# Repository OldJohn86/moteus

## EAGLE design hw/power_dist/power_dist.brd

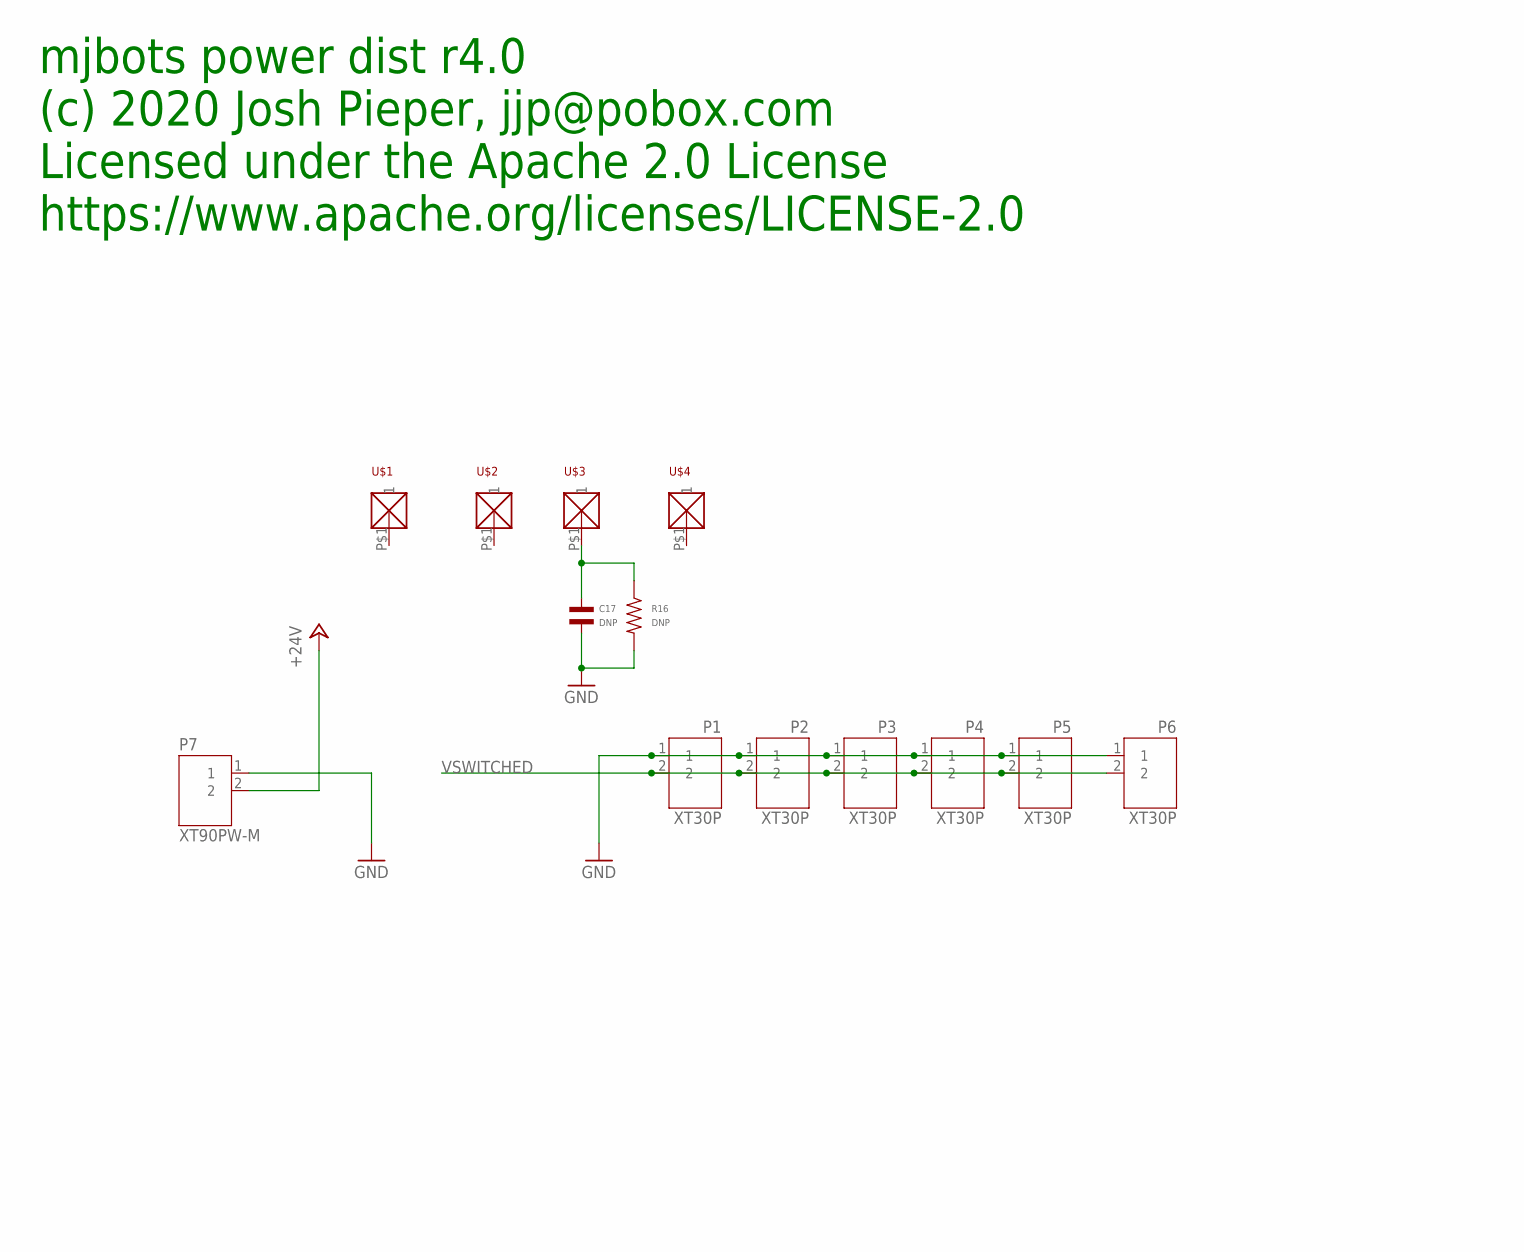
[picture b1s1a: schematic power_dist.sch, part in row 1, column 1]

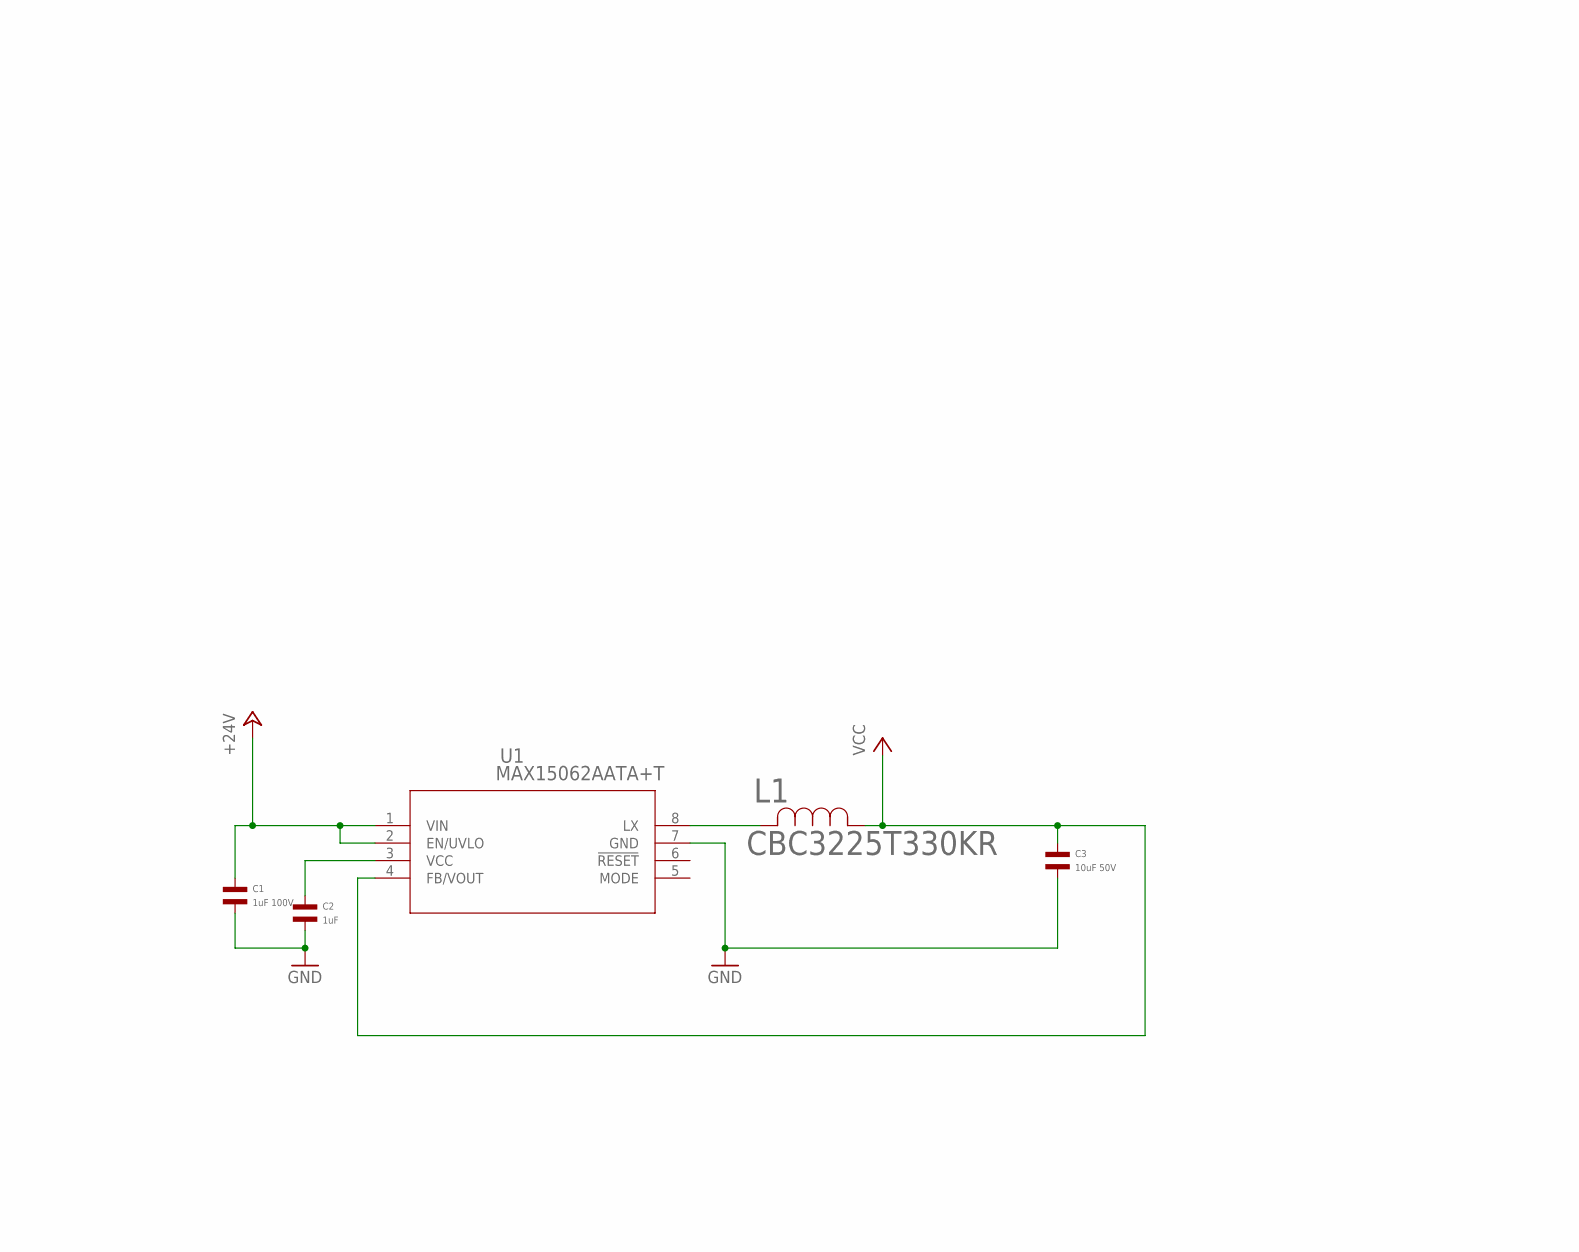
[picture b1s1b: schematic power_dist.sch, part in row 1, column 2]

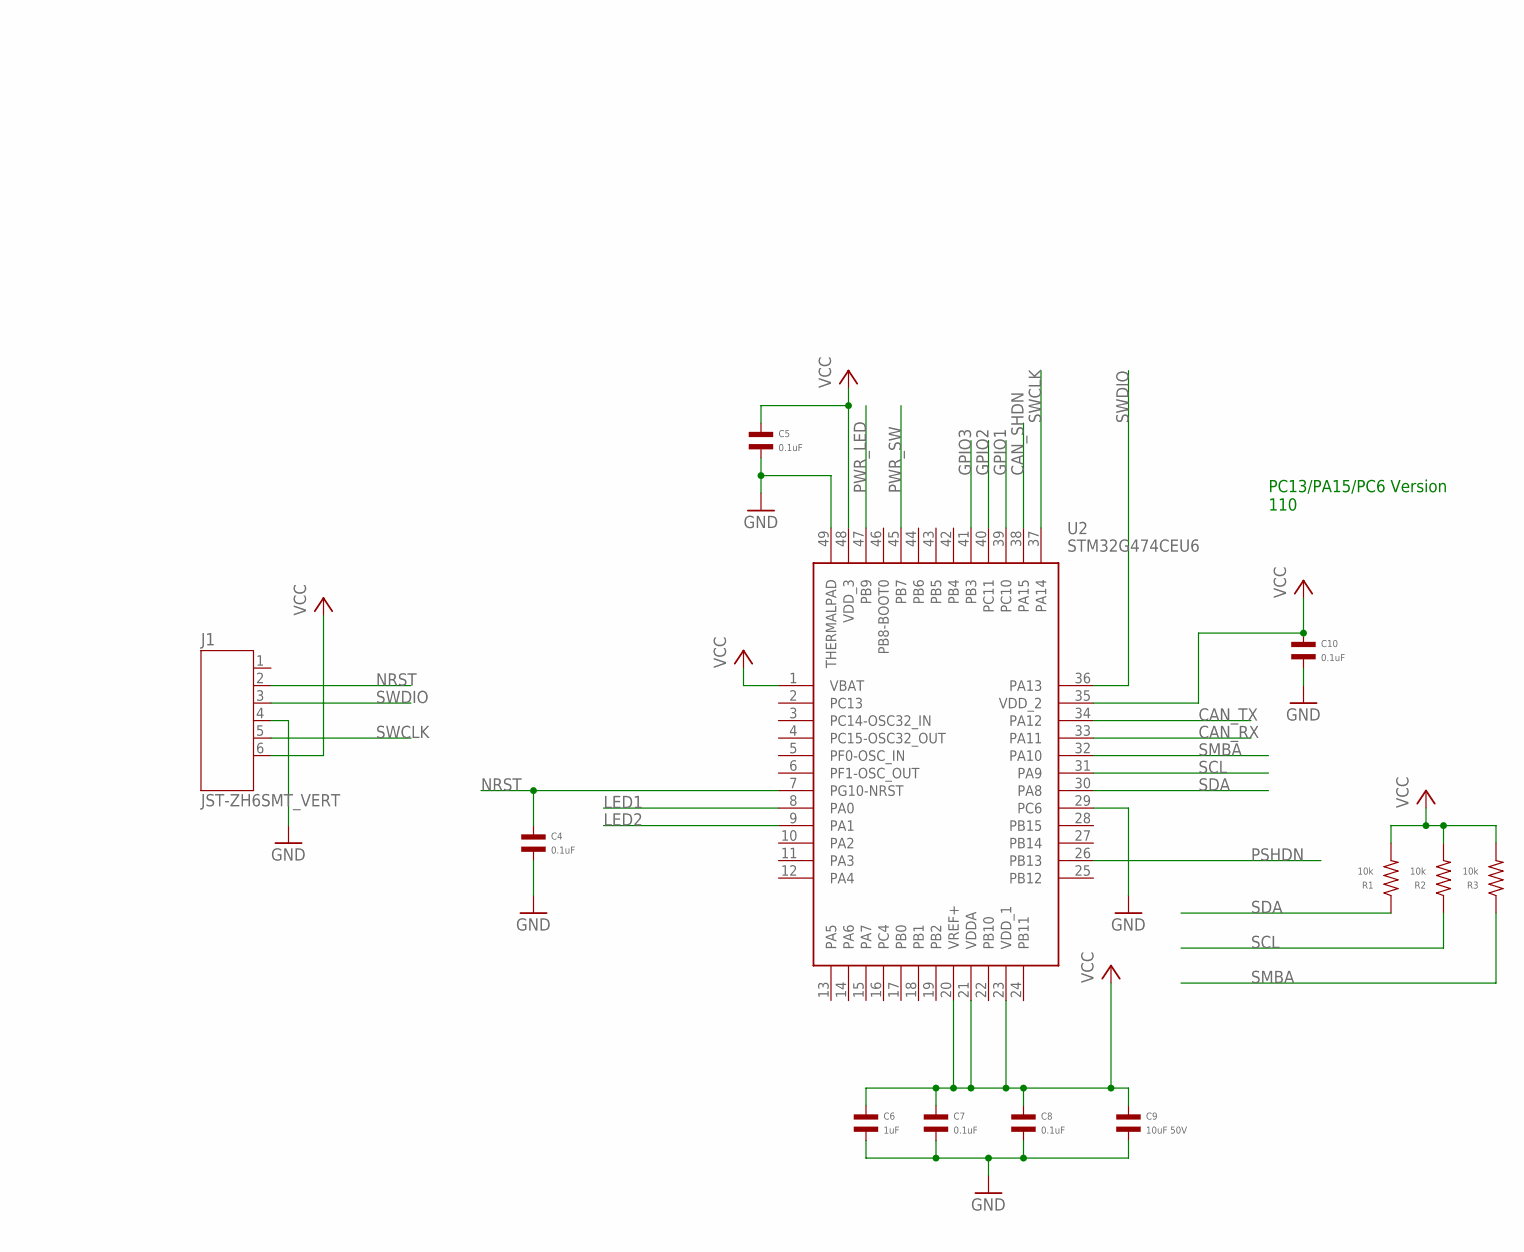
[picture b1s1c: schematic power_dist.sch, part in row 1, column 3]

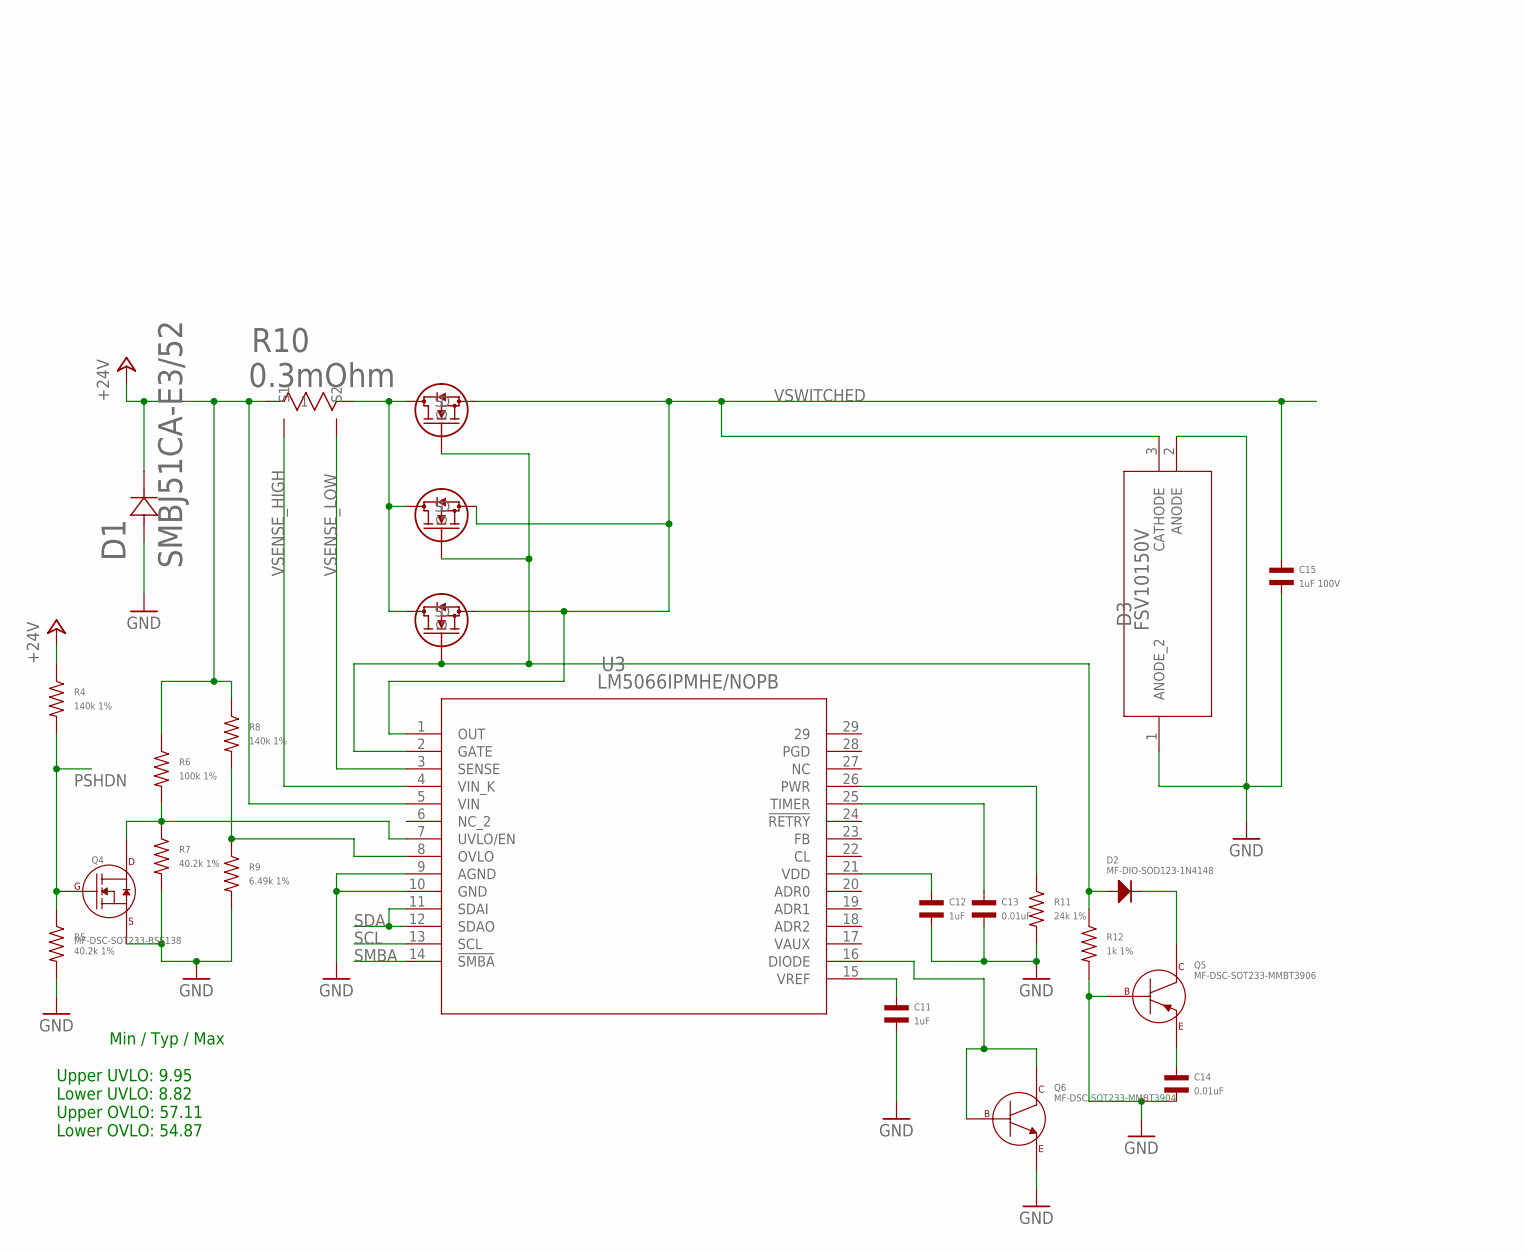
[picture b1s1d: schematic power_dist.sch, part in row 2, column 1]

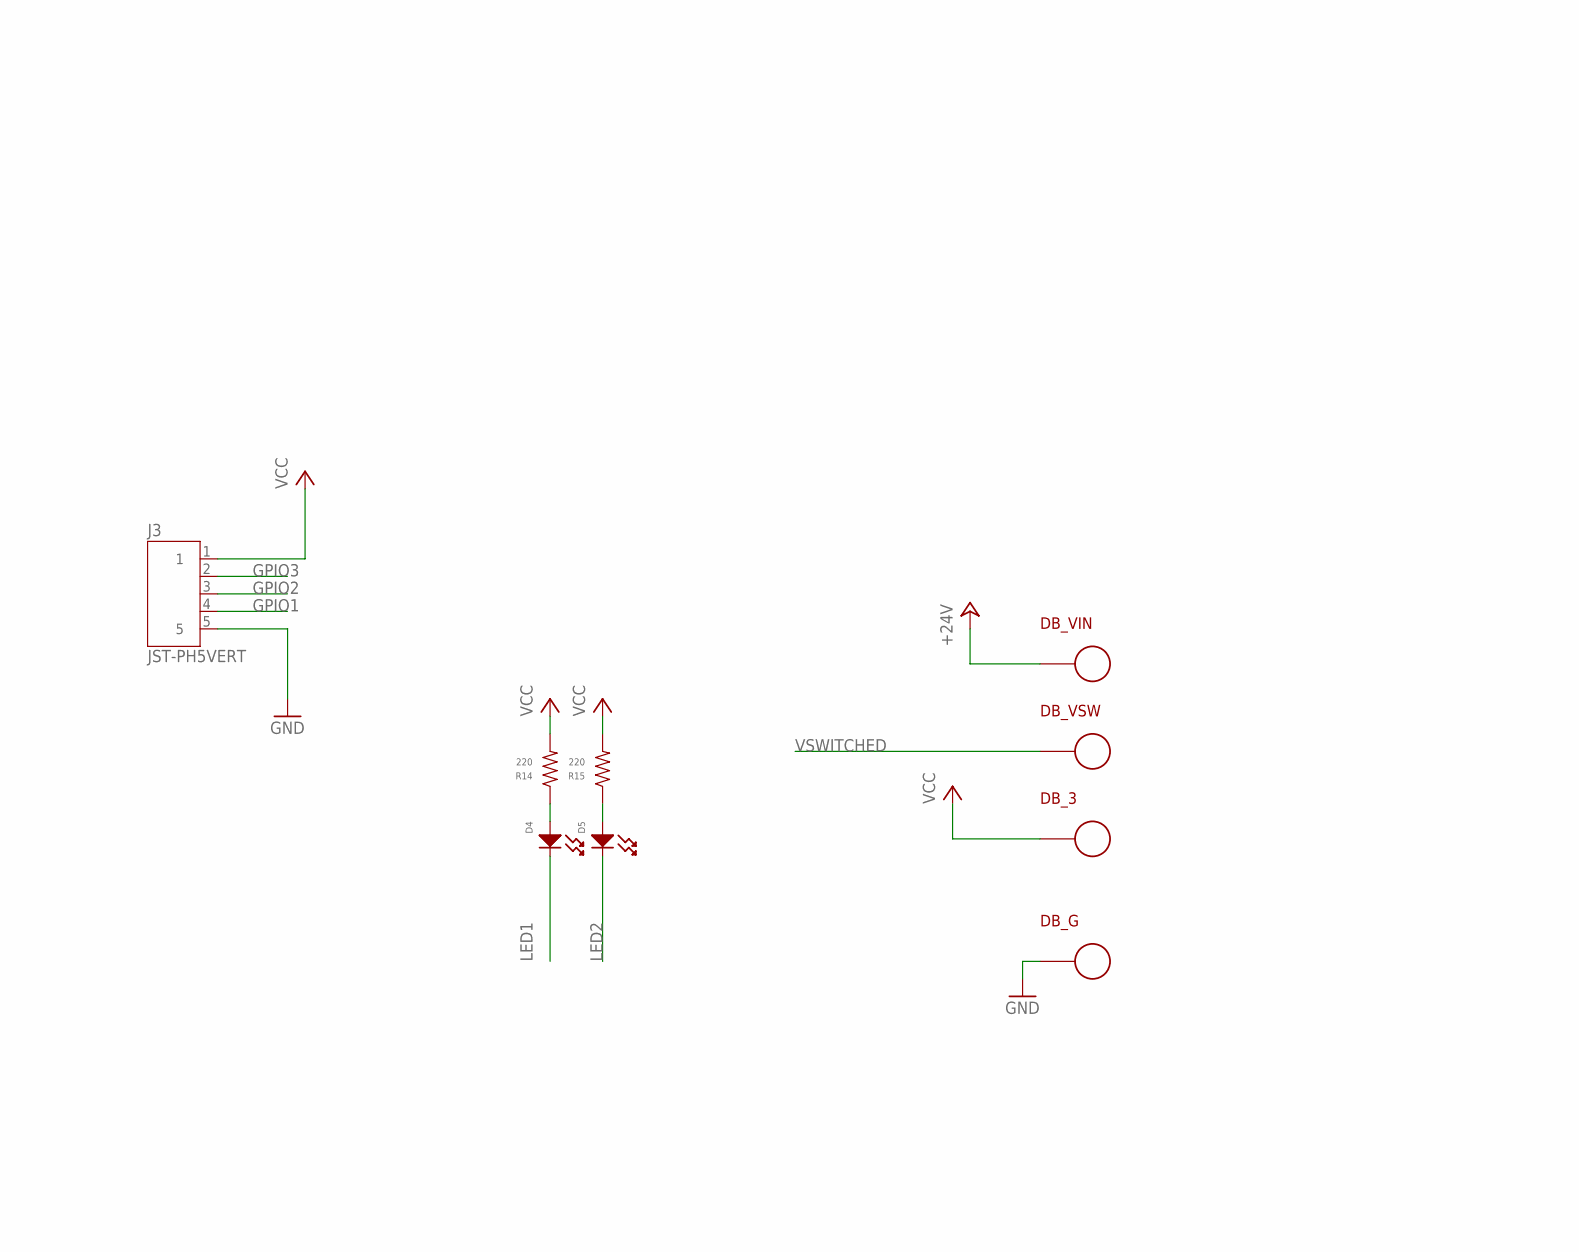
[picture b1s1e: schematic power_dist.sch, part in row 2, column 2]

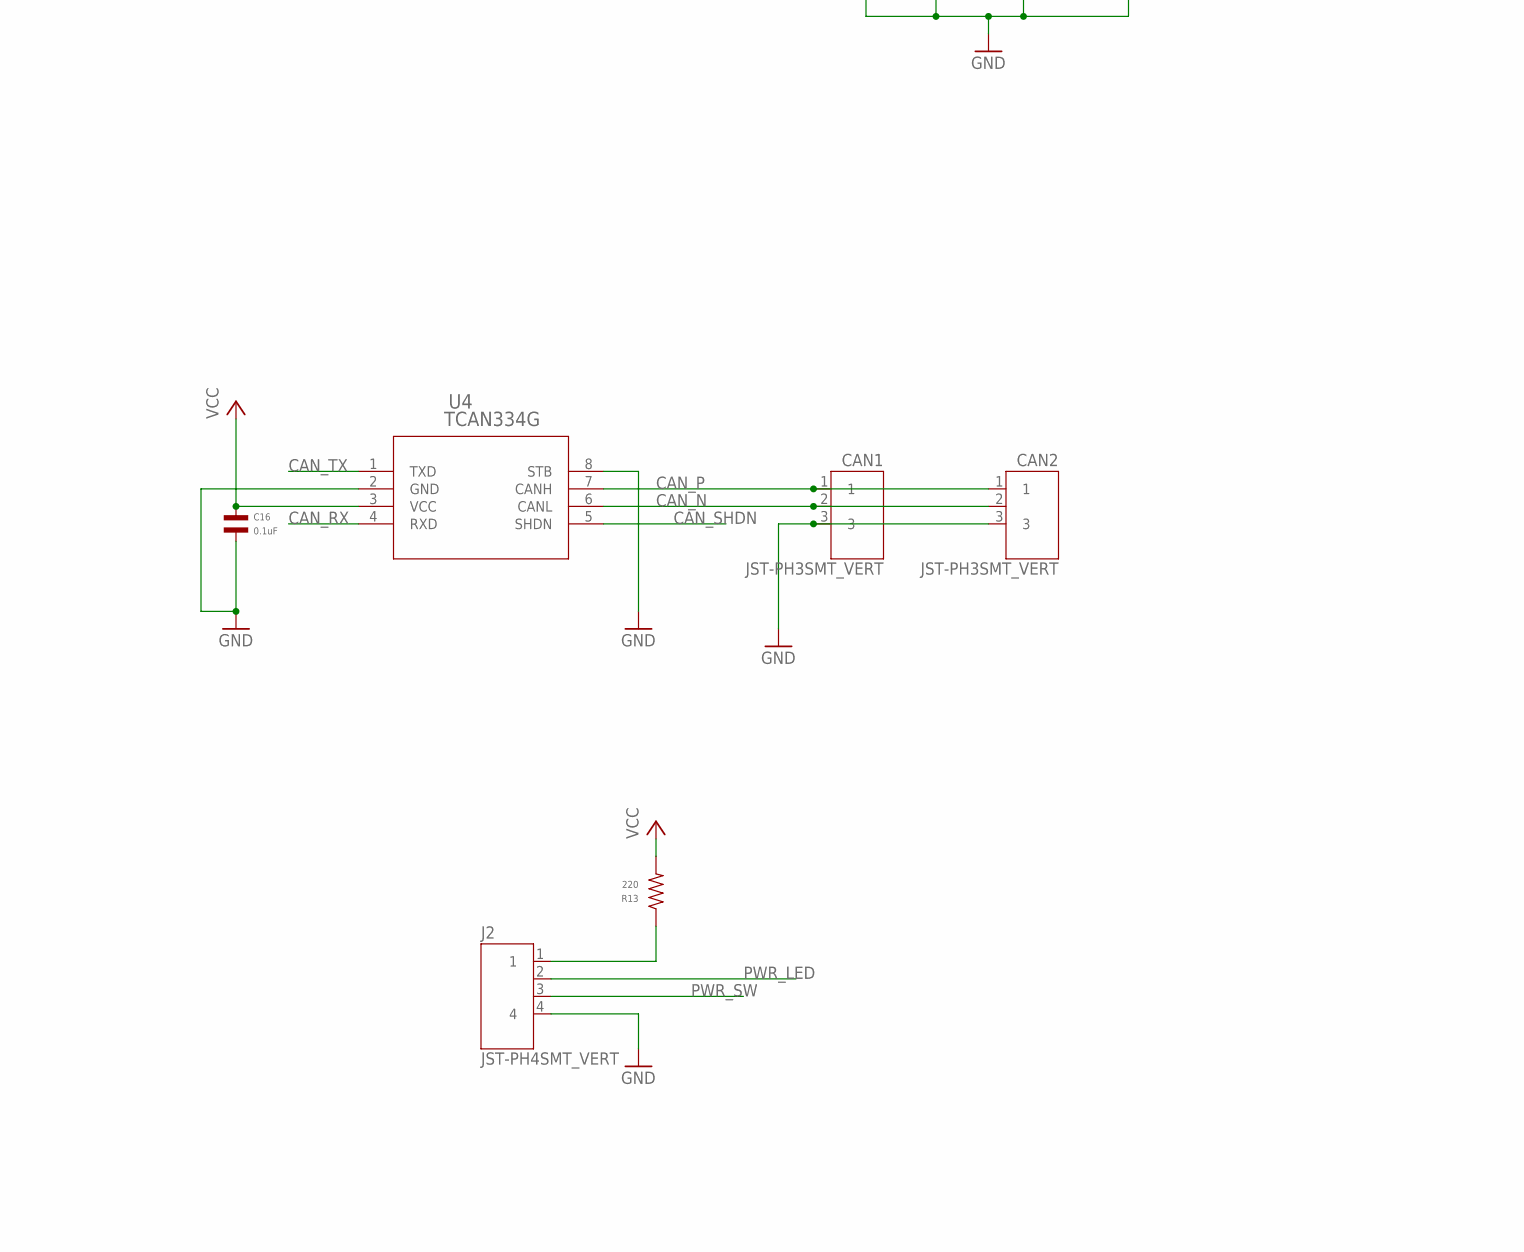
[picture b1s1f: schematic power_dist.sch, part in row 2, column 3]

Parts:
C1, C15: 1uF 100V; C0805; MPN GCM21BC72A105KE36L
C2, C6, C11, C12: 1uF; C0603; MPN MF-CAP-0603-1uF
C3, C9: 10uF 50V; C1206; MPN C3216X7R1H106K160AE
C4, C5, C7, C8, C10, C16: 0.1uF; C0603; MPN MF-CAP-0603-0.1uF
C13, C14: 0.01uF; C0603; MPN MF-CAP-0603-0.01uF
C17: DNP; C0603
CAN1, CAN2: JST-PH3SMT_VERT; JST_B3B_PH-SM4-TB(LF)(SN); MPN B3B-PH-SM4-TB(LF)(SN)
D1: SMBJ51CA-E3/52; DIODE_DO-214AC; MPN SMBJ51CA-E3/52
D2: MF-DIO-SOD123-1N4148; SOD-123
D3: FSV10150V; TO277-3L_ONS; MPN FSV10150V
D4, D5: LED_SINGLE-0603; LED0603; MPN MF-LED-0603-RED
DB_3: PAD24AWG_PAD; 24AWG_PAD
DB_G: PAD24AWG_PAD; 24AWG_PAD
DB_VIN: PAD24AWG_PAD; 24AWG_PAD
DB_VSW: PAD24AWG_PAD; 24AWG_PAD
J1: JST-ZH6SMT_VERT; JST_B6B-ZR-SM4-TF(LF)(SN); MPN B6B-ZR-SM4-TF(LF)(SN)
J2: JST-PH4SMT_VERT; JST_B4B_PH-SM4-TB(LF)(SN); MPN B4B-PH-SM4-TB(LF)(SN)
J3: JST-PH5VERT; JST_B5B_PH-SM4-TB(LF)(SN); MPN B5B-PH-SM4-TB(LF)(SN)
L1: CBC3225T330KR; IND_TAIYO_CBC3225_TAY; MPN CBC3225T330KR
P1, P2, P3, P4, P5, P6: XT30P; MPN XT30UPB-F
P7: XT90PW-M
Q1, Q2, Q3: PSMN4R8-100BSEJ; D2PAK_SOT404_NEX; MPN PSMN4R8-100BSEJ
Q4: MF-DSC-SOT233-BSS138; SOT-23-3
Q5: MF-DSC-SOT233-MMBT3906; SOT-23-3
Q6: MF-DSC-SOT233-MMBT3904; SOT-23-3
R1, R2, R3: 10k; R0603; MPN MF-RES-0603-10K
R4, R8: 140k 1%; R0603; MPN RC0603FR-07140KL
R5, R7: 40.2k 1%; R0603; MPN RC0603FR-0740K2L
R6: 100k 1%; R0603; MPN RC0603FR-07100KL
R9: 6.49k 1%; R0603; MPN RC0603FR-076K49L
R10: 0.3mOhm; SHUNT2512; MPN WSLF2512L3000FEA
R11: 24k 1%; R0603; MPN RC0603FR-0724KL
R12: 1k 1%; R0603; MPN RC0603FR-071KL
R13, R14, R15: 220; R0603; MPN MF-RES-0603-220
R16: DNP; R0603
U1: MAX15062AATA+T; 21-0487A_MXM; MPN MAX15062AATA+T
U2: STM32G474CEU6; QFN50P700X700X60-49N; MPN STM32G474CEU6
U3: LM5066IPMHE/NOPB; MXA28A_TEX; MPN LM5066IPMHE/NOPB
U4: TCAN334G; SOIC8; MPN LTC2875IS8
U$1, U$2, U$3, U$4: MOUNT; M2.5MOUNT

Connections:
+24V: C1.P$1, D1.1, DB_VIN.P$1, P7.2, R4.P$1, R6.P$1, R8.P$1, R10.1, U1.1 (VIN), U1.2 (EN/UVLO), U3.5 (VIN)
CAN_N: CAN1.2, CAN2.2, U4.6 (CANL)
CAN_P: CAN1.1, CAN2.1, U4.7 (CANH)
CAN_RX: U2.33 (PA11), U4.4 (RXD)
CAN_SHDN: U2.38 (PA15), U4.5 (SHDN)
CAN_TX: U2.34 (PA12), U4.1 (TXD)
GPIO1: J3.4, U2.39 (PC10)
GPIO2: J3.3, U2.40 (PC11)
GPIO3: J3.2, U2.41 (PB3)
LED1: D4.CATHODE, U2.8 (PA0)
LED2: D5.CATHODE, U2.9 (PA1)
unnamed: L1.2, U1.8 (LX)
unnamed: J2.1, R13.P$1
unnamed: Q6.P$1 (BASE), Q6.P$3 (COLLECTOR), U3.16 (DIODE)
unnamed: C2.P$1, U1.3 (VCC)
unnamed: D2.ANODE, Q1.1 (G), Q2.1 (G), Q3.1 (G), R12.P$1, U3.2 (GATE)
unnamed 16: U3.23 (FB); also elsewhere on the board
unnamed: C11.P$1, U3.15 (VREF)
unnamed: D4.ANODE, R14.P$1
unnamed: Q4.P$3 (DRAIN), R6.P$2, R7.P$1, U3.7 (UVLO/EN)
unnamed: R11.P$1, U3.26 (PWR)
unnamed: C13.P$1, U3.25 (TIMER)
unnamed 22: U3.28 (PGD); also elsewhere on the board
unnamed: D5.ANODE, R15.P$1
unnamed: C17.P$1, R16.P$1, U$3.P$1
NRST: C4.P$1, J1.2, U2.7 (PG10-NRST)
PSHDN: Q4.P$1 (GATE), R4.P$2, R5.P$1, U2.26 (PB13)
PWR_LED: J2.2, U2.47 (PB9)
PWR_SW: J2.3, U2.45 (PB7)
SCL: R2.P$1, U2.31 (PA9), U3.13 (SCL)
SDA: R1.P$1, U2.30 (PA8), U3.11 (SDAI), U3.12 (SDAO)
SMBA: R3.P$1, U2.32 (PA10), U3.14 (!SMBA)
SWCLK: J1.5, U2.37 (PA14)
SWDIO: J1.3, U2.36 (PA13)
VCC: C3.P$1, C5.P$1, C6.P$1, C7.P$1, C8.P$1, C9.P$1, C10.P$1, C16.P$1, DB_3.P$1, J1.6, J3.1, L1.1, R1.P$2, R2.P$2, R3.P$2, R13.P$2, R14.P$2, R15.P$2, U1.4 (FB/VOUT), U2.1 (VBAT), U2.20 (VREF+), U2.21 (VDDA), U2.23 (VDD_1), U2.35 (VDD_2), U2.48 (VDD_3), U4.3 (VCC)
VDD: C12.P$1, U3.21 (VDD); also elsewhere on the board
VIN_POST: Q1.2 (D), Q2.2 (D), Q3.2 (D), R10.2
VIN_SENSE: R8.P$2, R9.P$1, U3.8 (OVLO)
VSENSE_HIGH: R10.3 (S1), U3.4 (VIN_K)
VSENSE_LOW: R10.4 (S2), U3.3 (SENSE)
VSWITCHED: C15.P$1, D3.3 (CATHODE), DB_VSW.P$1, P1.2, P2.2, P3.2, P4.2, P5.2, P6.2, Q1.3 (S), Q2.3 (S), Q3.3 (S), U3.1 (OUT); also elsewhere on the board

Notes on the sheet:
mjbots power dist r4.0 (c) 2020 Josh Pieper, jjp@pobox.com Licensed under the Apache 2.0 License https://www.apache.org/licenses/LICENSE-2.0
Min / Typ / Max Upper UVLO: 9.95 Lower UVLO: 8.82 Upper OVLO: 57.11 Lower OVLO: 54.87
PC13/PA15/PC6 Version 110

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
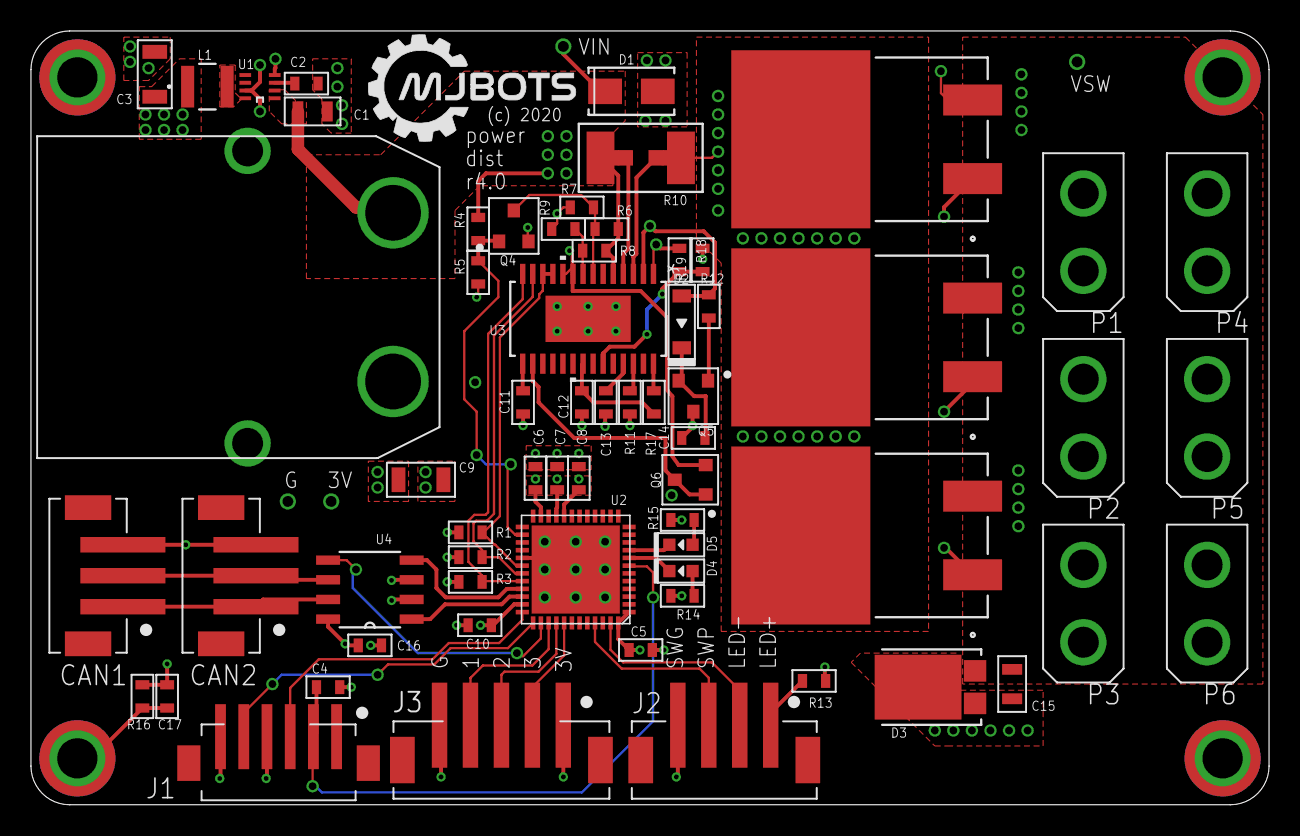
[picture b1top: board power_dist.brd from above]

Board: 4 copper layers, 80.0 x 50.0 mm, 72 parts (0 on the bottom side), 44 nets.

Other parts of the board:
R17, R18, R19: DNP; R0603

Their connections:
unnamed 16: R18.P$2, R19.P$1; also elsewhere on the board
unnamed 22: R17.P$2; also elsewhere on the board
VDD: R17.P$1; also elsewhere on the board
VSWITCHED: R18.P$1; also elsewhere on the board

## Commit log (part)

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2020-08-13 Update bazel_deps
2020-08-13 Update fdcanusb_register_example for protocol changes made in March
2020-08-13 fdcanusb_register_example: Report mode as an int
2020-08-13 Update TODO
2020-08-14 Add ubuntu 20.04 package list, and update host compilation instructions
2020-08-14 ubuntu 20.04 minimal installs don't have gcc either
2020-08-14 Yet more focal packages
2020-08-14 Update copyright year
2020-08-14 With PySide2, this draw workaround is no longer required
    Further, it actually breaks things in Ubuntu 20.04
2020-08-14 More packages for the install list
2020-08-14 Stub of a dynamometer drive
2020-08-15 Get dynamometer_drive to record data from multiple controllers
2020-08-15 Log data from the torque transducer
2020-08-15 Implement beginnings of static torque ripple test cycle
2020-08-15 Draft of a script to process static torque ripple results
2020-08-15 Write meta-data into plot
2020-08-15 Improve static torque ripple test cycle
    * Test with "d stop"
    * Test with torque in both directions
    * Actually handle parsing errors from transducer
2020-08-15 Tare the torque transducer at each power-on
2020-08-15 Support comparing ripple or error
2020-08-16 Make tview able to send commands on Ubuntu 20.04
2020-08-16 Add a theory of operation
2020-08-17 Slightly tweak up the minimum sample time after some trial and error experimentation
2020-08-17 Add a test cycle for verifying the pwm cycle overrun value
2020-08-18 Make the SPI mode be configurable
2020-08-18 moteus_tool: Calibration improvements
    * Actually pass the calibration speed to the correct 'd' command
    * Optionally emit the entirety of the calibration dataset to a file
    * --verbose should write all emissions, not just ack'd ones
2020-08-18 Make moteus_tool calibration not barf on possible new fields
    The board may in the future emit additional data per line. Now,
    moteus_tool won't die if sees extra things, it will just ignore them.
2020-08-18 Report more information during the calibration cycle
    Now when calibrating, we report at 100Hz instead of 50Hz, and we
    report the 3 phase currents at each time step in addition to the
    commanded phase and encoder reading. This should be enough
    information to calibrate anti-cogging in addition to the DQ transform.
2020-08-18 A script to plot phase currents from a version '2' calibration
2020-08-18 Remove now unused debug configuration
2020-08-18 Report the total percentage of the control cycle used
2020-08-18 Factor out file parsing so it can be unit tested
    Also, parse the new current information
2020-08-22 The "motor-not-configured" fault should trip in vdq mode too
2020-08-22 Doc tweak for correctness
2020-08-22 Config for 4114 motor
2020-08-22 I found a board for which a 6x ADC prescaler was needed... sigh
2020-08-22 Add another TODO
2020-08-22 Discard the very first calibration entry
    Experimentation has shown it to be largely bogus
2020-08-22 Add a way to flip signs when analyzing torque ripple tests
2020-08-22 When restoring config, keep going if some options are not present
    Previously, if a configurable option was removed, moteus_tool would
    immediately halt trying to set the remaining options, potentially
    losing much of the config it attempted to save.
2020-08-22 Add option to restore from saved calibration
2020-08-23 Provide an option to change the sign of the torque transducer
2020-08-23 Oops, typo
2020-08-23 Switch moteus_tool to get structured data via the binary interface
2020-08-27 Make tview work on either Ubuntu 18.04 or 20.04
2020-09-01 Rev the upper and lower leg for additional strength
2020-09-01 Add an automated test cycle for PWM mode
2020-09-01 Report commanded feedforward torque using torque scaling
2020-09-02 Add some debugging registers to report the intermediate PID values
2020-09-02 Switch the default cpu back to k8 to match the devkit video
2020-09-02 Do the current test while in motion in addition to stationary
2020-09-03 Initial bit of position mode validation
    This also adds a d term to the "rigid" mode for the fixture, which has
    been tested across all the things which use it.
2020-09-03 Add a kd verification step as well
2020-09-03 Add a ki test cycle to the position mode verification
2020-09-07 Enhance description of position mode in documentation
2020-09-07 More passes at lower leg
2020-09-07 Add a basic position mode validation cycle
2020-09-10 Beginning of a master firmware validation tool
2020-09-10 moteus_tool: Optionally do not store calibration
2020-09-10 Add all the easy cases to firmware_validate
2020-09-10 We need to run with no integrator during ripple tests
2020-09-10 Integrate the torque ripple test into the firmware validation script
2020-09-10 Actually fail when the dynanometer_drive tool fails
2020-09-10 Add a test cycle to verify low speed position mode control
    The performance here isn't great, so the initial tolerances are wide,
    and we don't even try to do it from non-zero start positions.
2020-09-10 WIP: Finish implementation of the "stay within" mode.
    This adds documentation, an automated test, and makes it not reset the
    current control loop when inside the bounds, which caused significant
    drag torque.
2020-09-10 Add a slight clarification to the "d within" documentation
2020-09-11 Actually stop the two devices if we have exceptions from any context
2020-09-11 Remove the kpkd_limit. No one needs it, and it takes up CPU cycles
2020-09-11 Tiny micro-optimizations
2020-09-11 More micro-optimizations
    Wait less for ADCs and stop writing to the DAC which never gets used
2020-09-11 Slightly expand some test tolerances
2020-09-11 Implement a "stay within bounds" mode
    This creates a new control mode that operates to control 0 torque
    (modulo feedforward) when the position is between two bounds. Outside
    of that region, the normal PID controller is used to force the
    position back to one of the bounds.
    One or both (not sure why) of the bounds can be nan to create
    one-sided regions. A feedforward torque can also be used which will
2020-09-11 Add a section to the reference manual discussing the limits of the controller
2020-09-11 Update travis-ci to use the correct build line for target
2020-09-12 Initial work on r4.5
2020-09-12 I'm not sure why yet, but we have to stop ADC4 for it to read reliably
2020-09-12 Implement a debug way to send kPwm (called "raw" in the cli) commands
2020-09-12 Improve default drive strength and timing
    This gives better power efficiency and performance across the rated
    input voltage range.
2020-09-12 Nope, we really do need to wait for ADC4 to keep it working for some reason.
2020-09-14 Remove the "clock" command as it isn't needed and just took up a few cycles
2020-09-14 Express the desired ADC prescaler as a constant
2020-09-14 Fix ADC configuration problems.
    * We were accidentally configuring ADC4/5 to sample two consecutive
    channels when we wanted to just do one.
    * Ensure that all of the channels are set in single mode, not
    continuous.
    * We don't need to manually clear EOC, it will be cleared as soon as
    DR is read.
2020-09-14 Slightly increase a threshold
2020-09-14 Do our PWM overrun check after sampling is complete
    Previously we were waiting for the entire ADC conversion to complete
    which was overly conservative. This lets us get about a 20% higher
    maximum voltage out.
2020-09-15 Oops, forgot to serialize bounds_min and bounds_max
2020-09-16 Add test through holes for the CAN bus on a 2mm spacing
2020-09-21 r4.5 as sent to MF
2020-09-26 Update documentation to use correct mode number for position
2020-09-27 Update the link to the register documentation
2020-10-01 Add a solid model for the power dist board
2020-10-01 The qdd100 had a reducer
2020-10-03 Fix typo in doc
2020-10-05 Add the full path to moteus_tool in getting_started
2020-10-06 Update mjlib and bazel_deps
2020-10-08 More 3d prints
2020-10-08 Fix type in fdcanusb_register_example
2020-10-09 Document what register values are used if unspecified
2020-10-09 Add documentation for watchdog timeout config
2020-10-22 Remove reference to nonexistant register map
2020-10-22 Fix typo in config name
2020-10-22 Update mjlib to get socketcan working in moteus_tool
2020-10-22 Implement a cooldown period when removing power
    This leaves the motor in a "brake" configuration for a fixed number of
    cycles before disabling the motor driver. It is intended to reduce DC
    bus transients when stopping from high current.
    If the DRV8323 experiences an over-current fault, it internally uses a
    different mechanism to mitigate this by overriding the drive strength
    to a low value. We can't do that on the fly easily, so do this
2020-10-22 Use different default voltage configs for r4.5
2020-10-22 Add some 40V ripple qualification data
2020-10-24 Move velocity mapping to the common section
2020-10-24 Use a higher vds_lvl for r4.5 and later
2020-10-25 Update rules_mbed and start using bazel platforms
    Now, for host builds, we use a standalone LLVM bazel toolchain, which
    is an mjbots fork of https://github.com/grailbio/bazel-toolchain
    NOTE: This changes the required commands for building host and target
    exectuables. After this change, use `--config=host` or
    `--config=target` rather than the legacy `--cpu=FOO`.
2020-10-26 Add a missing header and get filesystem calls to work on Windows
2020-10-26 Upgrade bazel_deps and mjlib in support of eventual Windows compilation
2020-10-26 Support compilation of moteus_tool at least on Windows
2020-10-26 Select a useful default serial port on Windows for moteus_tool
2020-10-26 Remove an unused variable
2020-10-28 Switch to use the native.existing_rule pattern
    This makes our diamond dependency handling more robust, as
    dependencies don't have to be manually excluded in a hard to determine
    way depending upon the entire transitive closure.
2020-10-29 Only consider serial ports that have a COM designator
    On some machines, the USB serial port has multiple listings,
    some with a COMN identifier and others without. Now we only look
    at those that can actually be used.
2020-10-29 Tweak lower leg to be in PC with variable infill
2020-10-29 Add a .step file for the qdd100
2020-10-29 Remove historical TODO notes
2020-10-29 We implemented unlimited rotation
2020-11-06 Update the build command in make_release
2020-11-11 The power_dist board doesn't sleep
2020-11-13 Dcoument that termination resistors may be necessary
2020-11-20 WIP of power_dist r4
2020-11-20 power_dist r4 rough layout and most things renumbered
2020-11-21 WIP checkpoint of power_dist r4
2020-11-21 power_dist r4: Checkpoint, most power/gnd routed
2020-11-21 power_dist r4: Resize and rough place silks
2020-11-21 power_dist r4: Routed and labels
2020-11-21 power_dist r4: Optionally ground one of the mounting holes
2020-11-21 power_dist r4: Assign part numbers
2020-11-21 power_dist r4: Update XT90 silk to be closer to actual part
2020-11-21 power_dist r4: Update to 6mm spacing
2020-11-21 power_dist r4: Pass ERC
2020-11-22 power_dist: Use VSAMP_OUT to monitor the pre-charge cycle
    This will fault if the pre-charge cycle fails. It also only works on
    boards that have been reworked to have the correct voltage sampling
    resistors installed. (r3.1 boards shipped prior to 2020-11-22 have
    incorrect sampling resistors installed).
2020-11-22 power_dist r4: Fix silk placement
2020-11-25 Building openocd can require libusb
2020-11-25 Snapshot of r4.0
2020-11-25 moteus_tool: Expose the polling rate as a cmdline flag
2020-11-30 Add the ability to trim the RC oscillator and a tool to calibrate it
2021-02-07 Add macs command for tview running
2026-06-15 Deployed d65e09e1 with MkDocs version: 1.6.1
2026-06-16 Deployed 6bfc3eee with MkDocs version: 1.6.1

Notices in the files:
parts and their libraries:
COPYRIGHT: Copyright (C) 2018 Accelerated Designs. All rights reserved
